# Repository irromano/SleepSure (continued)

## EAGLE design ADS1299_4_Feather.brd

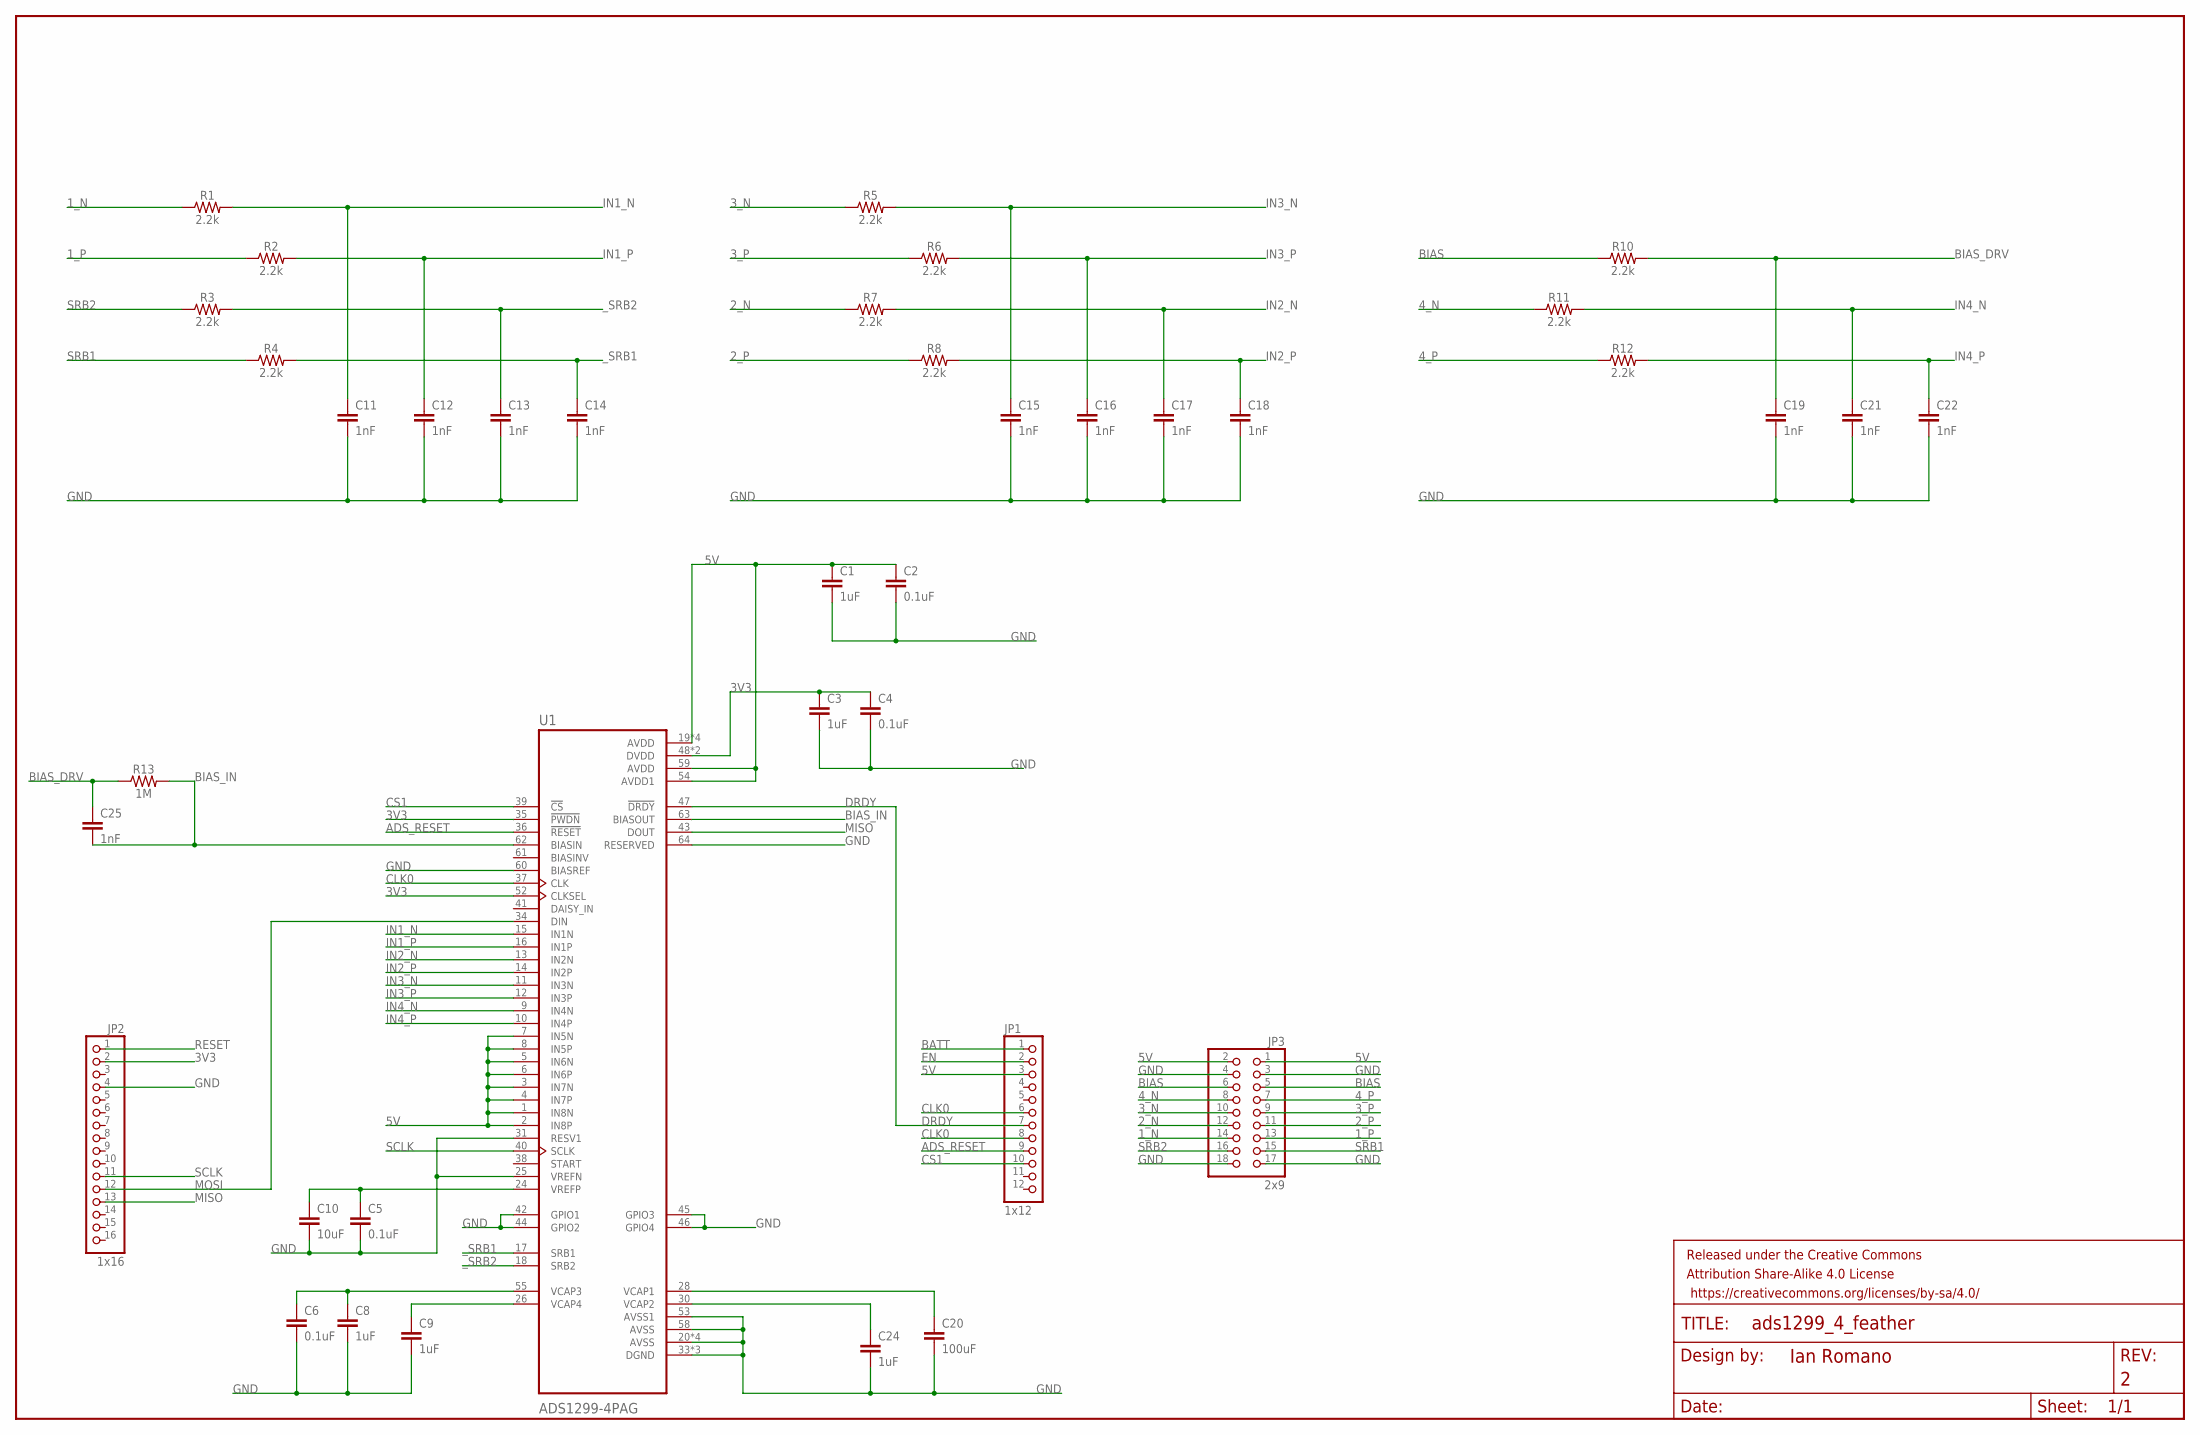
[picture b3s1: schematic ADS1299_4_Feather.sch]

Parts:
C1, C3, C8, C9, C24: 1uF; 0805
C2, C4, C5, C6: 0.1uF; 0805
C10: 10uF; 0805
C11, C12, C13, C14, C15, C16, C17, C18, C19, C21, C22, C25: 1nF; 0805
C20: 100uF; 0805
FRAME1: FRAME-LEDGER; CREATIVE_COMMONS
JP1: 1x12; MICROBUILDER_1X12_ROUND_76MIL
JP2: 1x16; MICROBUILDER_1X16_ROUND_76MIL
JP3: 2x9; 2X09-BIG
R1, R2, R3, R4, R5, R6, R7, R8, R10, R11, R12: 2.2k; 0805
R13: 1M; 0805
U1: ADS1299-4PAG; QFP50P1200X1200X120-64N

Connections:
1_N: JP3.14, R1.1
1_P: JP3.13, R2.1
2_N: JP3.12, R7.1
2_P: JP3.11, R8.1
3V3: C3.1, C4.1, JP2.2, U1.35 (!PWDN), U1.48 (DVDD), U1.50 (DVDD), U1.52 (CLKSEL)
3_N: JP3.10, R5.1
3_P: JP3.9, R6.1
4_N: JP3.8, R11.1
4_P: JP3.7, R12.1
5V: C1.1, C2.1, JP1.3, JP3.1, JP3.2, U1.1 (IN8N), U1.2 (IN8P), U1.3 (IN7N), U1.4 (IN7P), U1.5 (IN6N), U1.6 (IN6P), U1.7 (IN5N), U1.8 (IN5P), U1.19 (AVDD), U1.21 (AVDD), U1.22 (AVDD), U1.54 (AVDD1), U1.56 (AVDD), U1.59 (AVDD)
ADS_RESET: JP1.9, U1.36 (!RESET)
BATT: JP1.1
BIAS: JP3.5, JP3.6, R10.1
BIAS_DRV: C19.1, C25.1, R10.2, R13.1
BIAS_IN: C25.2, R13.2, U1.62 (BIASIN), U1.63 (BIASOUT)
CLK0: JP1.6, JP1.8, U1.37 (CLK)
CS1: JP1.10, U1.39 (!CS)
DRDY: JP1.7, U1.47 (!DRDY)
EN: JP1.2
GND: C1.2, C2.2, C3.2, C4.2, C5.2, C6.2, C8.2, C9.2, C10.2, C11.2, C12.2, C13.2, C14.2, C15.2, C16.2, C17.2, C18.2, C19.2, C20.2, C21.2, C22.2, C24.2, JP2.4, JP3.3, JP3.4, JP3.17, JP3.18, U1.20 (AVSS), U1.23 (AVSS), U1.25 (VREFN), U1.31 (RESV1), U1.32 (AVSS), U1.33 (DGND), U1.42 (GPIO1), U1.44 (GPIO2), U1.45 (GPIO3), U1.46 (GPIO4), U1.49 (DGND), U1.51 (DGND), U1.53 (AVSS1), U1.57 (AVSS), U1.58 (AVSS), U1.60 (BIASREF), U1.64 (RESERVED)
IN1_N: C11.1, R1.2, U1.15 (IN1N)
IN1_P: C12.1, R2.2, U1.16 (IN1P)
IN2_N: C17.1, R7.2, U1.13 (IN2N)
IN2_P: C18.1, R8.2, U1.14 (IN2P)
IN3_N: C15.1, R5.2, U1.11 (IN3N)
IN3_P: C16.1, R6.2, U1.12 (IN3P)
IN4_N: C21.1, R11.2, U1.9 (IN4N)
IN4_P: C22.1, R12.2, U1.10 (IN4P)
MISO: JP2.13, U1.43 (DOUT)
MOSI: JP2.12, U1.34 (DIN)
unnamed: C5.1, C10.1, U1.24 (VREFP)
unnamed: C24.1, U1.30 (VCAP2)
unnamed: C6.1, C8.1, U1.55 (VCAP3)
unnamed: C20.1, U1.28 (VCAP1)
unnamed: C9.1, U1.26 (VCAP4)
RESET: JP2.1
SCLK: JP2.11, U1.40 (SCLK)
SRB1: JP3.15, R4.1
SRB2: JP3.16, R3.1
_SRB1: C14.1, R4.2, U1.17 (SRB1)
_SRB2: C13.1, R3.2, U1.18 (SRB2)

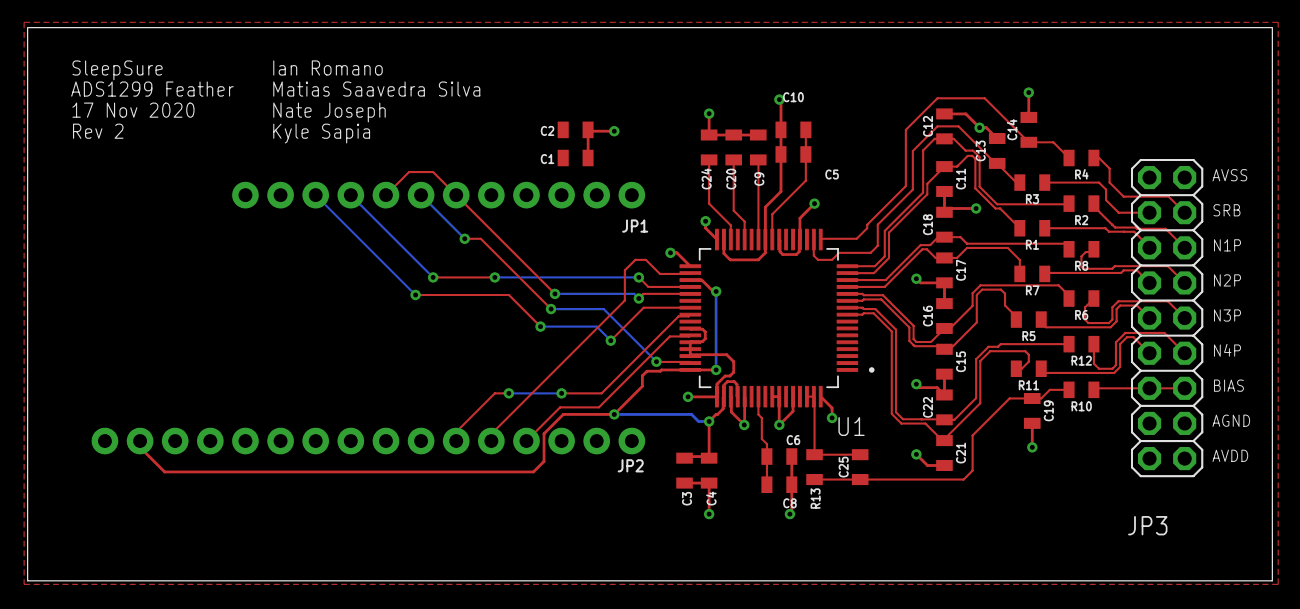
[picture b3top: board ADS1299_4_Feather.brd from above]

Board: 2 copper layers, 90.0 x 40.0 mm, 40 parts (0 on the bottom side), 38 nets.

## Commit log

2020-11-05 new file: ADS1299_4_Feather.brd
2020-11-05 modified: ADS1299_4_Feather.sch removed noise filters and changed component models
2020-11-16 modified: ADS1299_4_Feather.brd modified: ADS1299_4_Feather.sch
2020-11-16 new file: eagle.epf Adding Project file to be used with Eagle
2020-11-17 modified: ADS1299_4_Feather.brd Added pinout labels, team names and logo to silk screen
2020-11-18 modified: ADS1299_4_Feather.brd Moved soldermask layer to solder gerber group
2020-11-18 modified: ADS1299_4_Feather.brd Moved Logo so it's not cutoff from the board.
2020-11-18 modified: ADS1299_4_Feather.brd Removed excess color from logo
2020-12-08 Increased distance between adafruit mounting headers from 0.7" to 0.8"
    modified: ADS1299_4_Feather.brd
    modified: ADS1299_4_Feather.sch
2021-03-19 Changes to be committed: new file: ADS1299_feather/ADS1299_4_Feather.brd new file: ADS1299_feather/ADS1299_4_Feather.sch new file: ADS1299_feather/eagle.epf
    Changes not staged for commit:
    deleted: ADS1299_4_Feather.brd
    deleted: ADS1299_4_Feather.sch
    deleted: eagle.epf
    Untracked files:
    vim.exe.stackdump
2021-03-19 Delete eagle.epf
    Moved all feather files into feather folder
2021-03-19 Moved file to correct folder
2021-04-08 Added power booster to standalone board
2021-04-10 changed usb header'
2021-04-12 modified design file and removed errors
2021-04-12 changed footprint of 100uF caps to 1206
2021-04-12 added START pin of ADS1299 to gpio27
2021-04-17 Uploading final standalone and feather files
2021-04-17 Adding final standalone and feather board changes
2021-04-23 Adding ESP32 ADS1299 Arduino Library
2021-04-25 Added changes to match BME280 SPI demo
2021-04-25 Update BluetoothSend.ino
    Data loosely reflects input to machine learning algorithm
2021-04-25 Can now automatically select COM port
2021-04-29 Adding ADS1299 Arduino library written by SleepSure. Removing old EDS1299 library.
2021-04-29 Adding ADS1299 Arduino library
2021-04-29 Added write command to write registers. Expanded boot sequence to start continious data retrieval
2021-04-30 Now sends 8 channels of data
2021-04-30 Can now read data from 8 channels
2021-04-30 test
2021-04-30 Moved code into folder
2021-04-30 Removed unnecessary files
2021-04-30 Added Data folder
2021-05-02 Seizure Data
    Data into 5 categories
2021-05-04 Added continious mode to ADS1299 functionality
2021-05-08 Seizure Data
    Seizure Data uploaded
2021-05-08 MachineLearning Code
    Machine Learning Codes uploaded, deep learning (fail) and stat based
2021-05-08 Adding ADS1299 Library
2021-05-08 Updating library files
2021-05-09 Sends 5-byte packets
2021-05-09 Reads 5 byte packets
2021-05-09 Can correctly send 5-byte packets
2021-05-09 Plot data fixed
2021-05-11 Reducing SPI rate to 1M Hz which allows the registers to be written properly.
